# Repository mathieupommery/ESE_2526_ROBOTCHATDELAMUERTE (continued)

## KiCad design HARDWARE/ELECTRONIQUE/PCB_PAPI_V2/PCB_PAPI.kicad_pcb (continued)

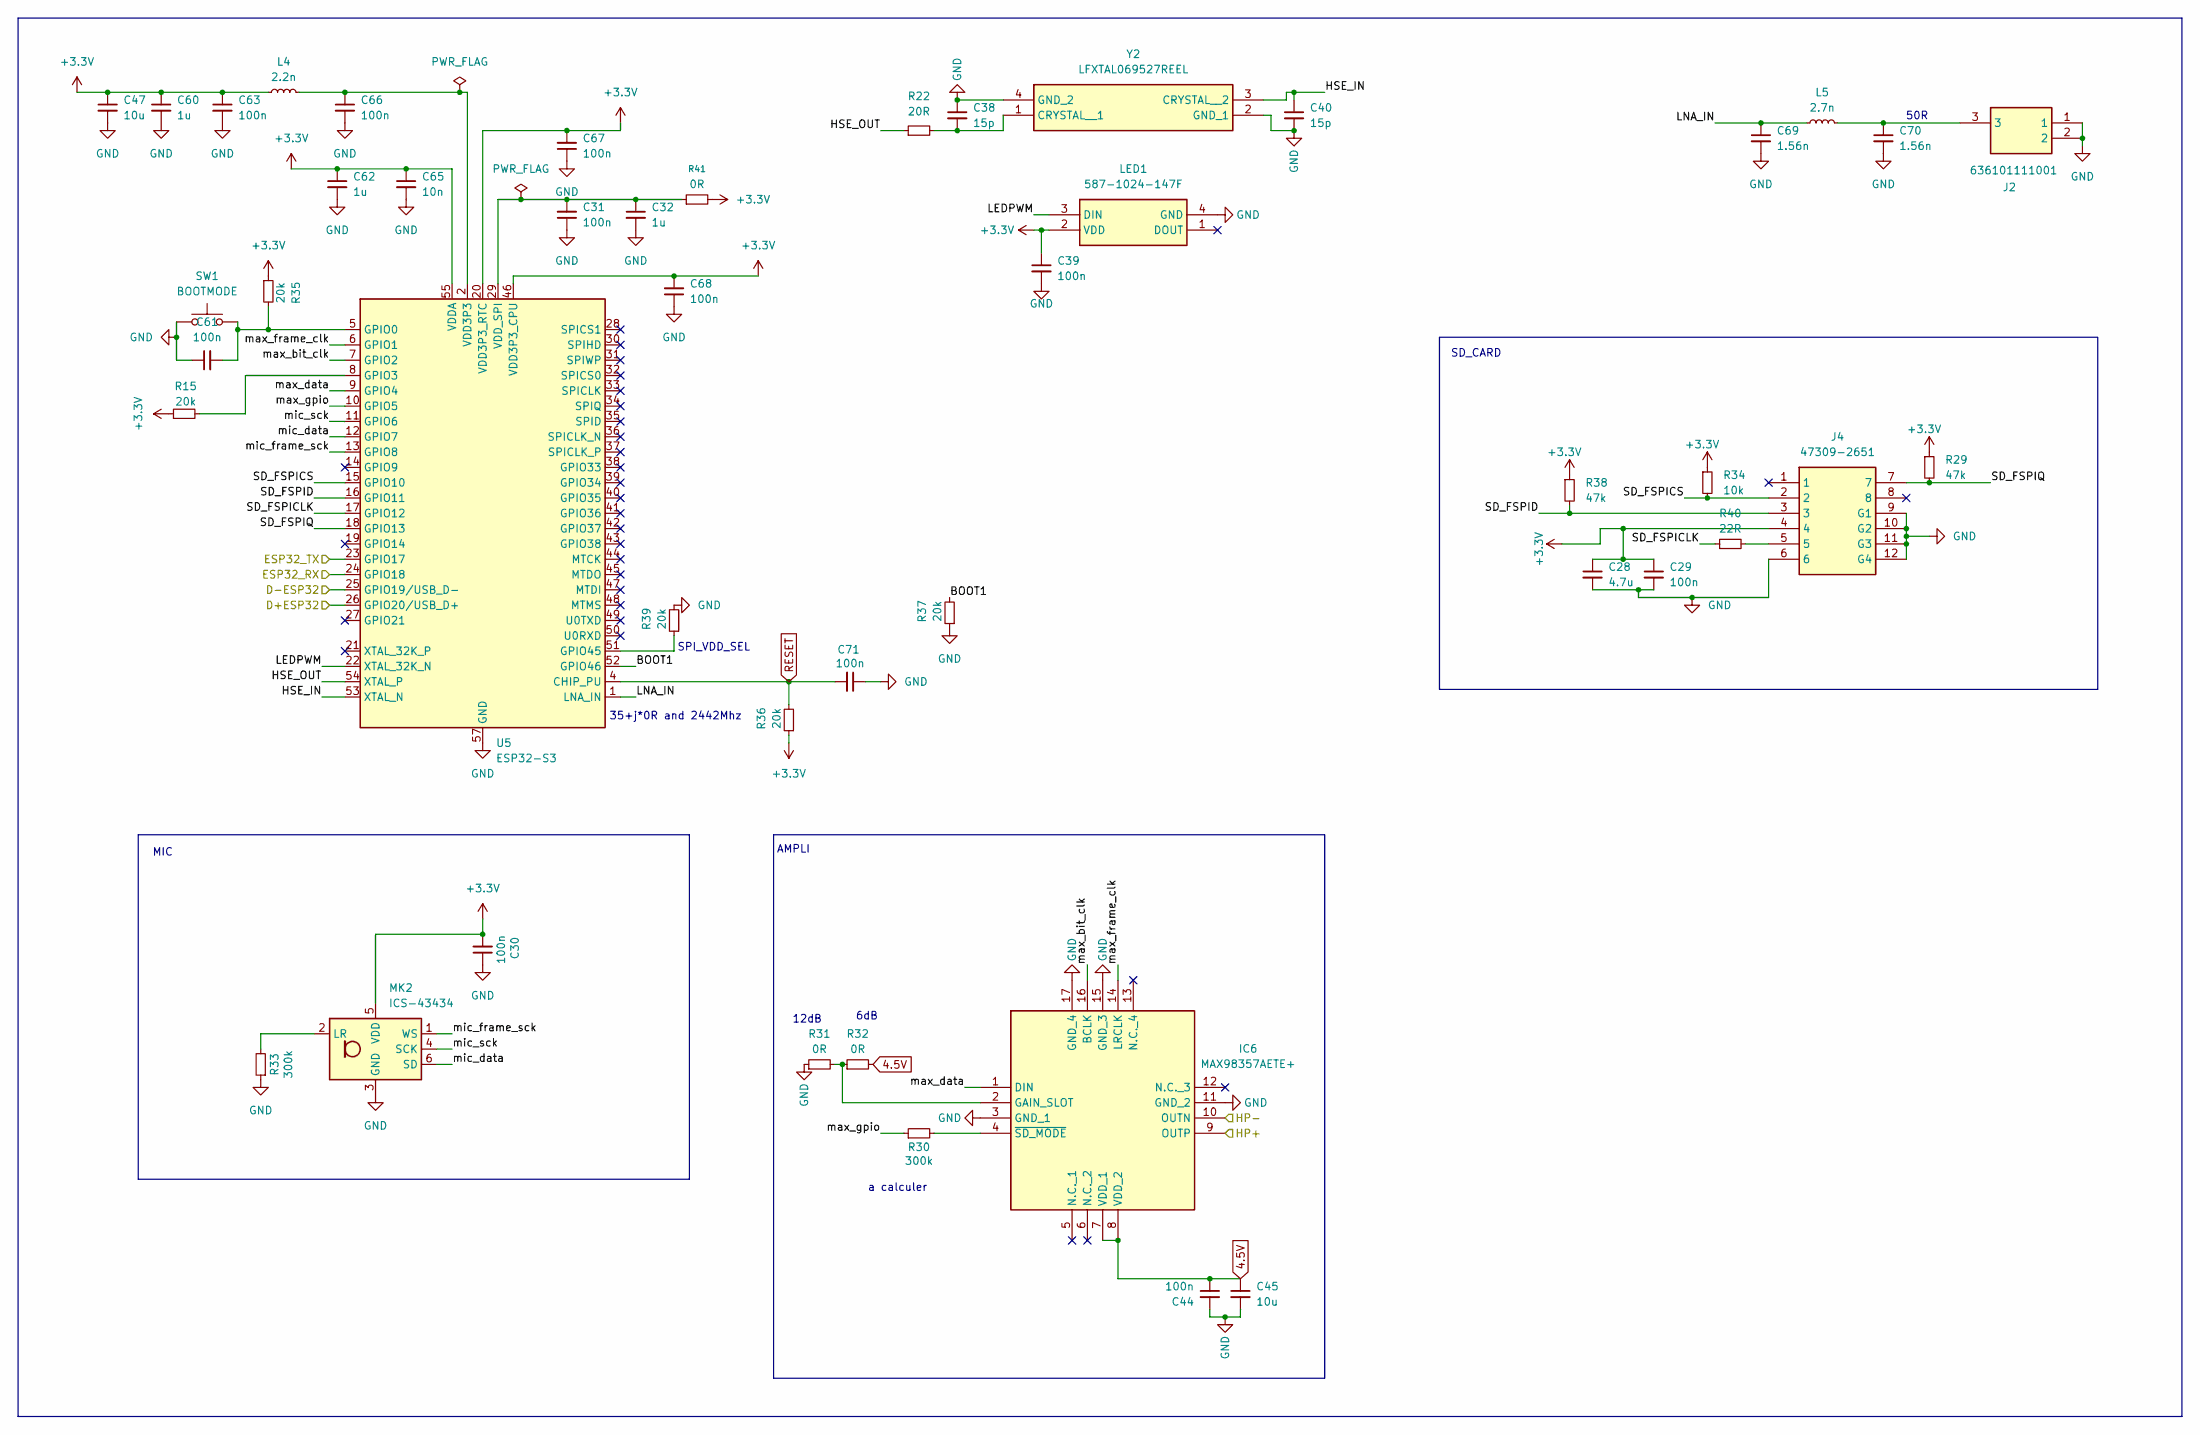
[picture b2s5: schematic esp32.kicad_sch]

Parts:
C28: 4.7u; C_0402_1005Metric_Pad0.74x0.62mm_HandSolder
C29, C39, C44: 100n; C_0201_0603Metric
C30, C31, C61, C63, C66, C67, C68, C71: 100n; C_0201_0603Metric_Pad0.64x0.40mm_HandSolder
C32, C60, C62: 1u; C_0402_1005Metric_Pad0.74x0.62mm_HandSolder
C38, C40: 15p; C_0201_custom
C45: 10u; C_0402_1005Metric; Manufacturer_Part_Number 885012105008; Mouser Part Number 710-885012105008
C47: 10u; C_0402_1005Metric_Pad0.74x0.62mm_HandSolder
C65: 10n; C_0201_0603Metric_Pad0.64x0.40mm_HandSolder
C69, C70: 1.56n; C_0402_1005Metric_Pad0.74x0.62mm_HandSolder
IC6: MAX98357AETE+; QFN50P300X300X80-17N; Manufacturer_Part_Number MAX98357AETE+; Mouser Part Number 700-MAX98357AETE+
J2: 636101111001; Mouser Part Number 710-636101111001
J4: 47309-2651; 473092651; Manufacturer_Part_Number 47309-2651
L4: 2.2n; L_0603_1608Metric
L5: 2.7n; L_0603_1608Metric
LED1: 587-1024-147F; 5871024147F; Manufacturer_Part_Number 587-1024-147F
MK2: ICS-43434; InvenSense_ICS-43434-6_3.5x2.65mm
R15, R35, R36, R37, R39: 20k; R_0201_0603Metric_Pad0.64x0.40mm_HandSolder
R22: 20R; R_0201_0603Metric
R29, R38: 47k; R_0201_0603Metric
R30, R33: 300k; R_0201_0603Metric; Manufacturer_Part_Number ERJ-1GNF1000C; Mouser Part Number 667-ERJ-1GNF1000C
R31: 0R; R_0201_custom; Manufacturer_Part_Number ERJ-1GNF1000C; Mouser Part Number 667-ERJ-1GNF1000C
R32: 0R; R_0201_0603Metric; Manufacturer_Part_Number ERJ-1GNF1000C; Mouser Part Number 667-ERJ-1GNF1000C
R34: 10k; R_0201_0603Metric
R40: 22R; R_0201_0603Metric
R41: 0R; R_0402_1005Metric_Pad0.72x0.64mm_HandSolder
SW1: BOOTMODE; KXT341LHS
U5: ESP32-S3; QFN-56-1EP_7x7mm_P0.4mm_EP4x4mm
Y2: LFXTAL069527REEL; Manufacturer_Part_Number LFXTAL069527REEL

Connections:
4.5V: C44.1, C45.1, IC6.7 (VDD_1), IC6.8 (VDD_2), R32.2; also elsewhere on the board
+3.3V: C28.1, C29.1, C30.2, C39.1, C47.1, C60.1, C62.1, C63.1, C65.1, C67.2, C68.2, J4.4, L4.1, LED1.2 (VDD), MK2.5 (VDD), R15.1, R29.1, R34.1, R35.1, R36.1, R38.1, R41.2, U5.20 (VDD3P3_RTC), U5.46 (VDD3P3_CPU), U5.55 (VDDA), U5.56 (VDDA); also elsewhere on the board
/D+ESP32: U5.26 (GPIO20/USB_D+); also elsewhere on the board
/D-ESP32: U5.25 (GPIO19/USB_D-); also elsewhere on the board
/ESP32/BOOT1: R37.2, U5.52 (GPIO46)
/ESP32/HSE_IN: C40.1, U5.53 (XTAL_N), Y2.3 (CRYSTAL__2)
/ESP32/HSE_OUT: R22.1, U5.54 (XTAL_P)
/ESP32/LEDPWM: LED1.3 (DIN), U5.22 (XTAL_32K_N)
/ESP32/LNA_IN: C69.1, L5.1, U5.1 (LNA_IN)
/ESP32/SD_FSPICLK: R40.1, U5.17 (GPIO12)
/ESP32/SD_FSPICS: J4.2, R34.2, U5.15 (GPIO10)
/ESP32/SD_FSPID: J4.3, R38.2, U5.16 (GPIO11)
/ESP32/SD_FSPIQ: J4.7, R29.2, U5.18 (GPIO13)
/ESP32/max_bit_clk: IC6.16 (BCLK), U5.7 (GPIO2)
/ESP32/max_data: IC6.1 (DIN), U5.9 (GPIO4)
/ESP32/max_frame_clk: IC6.14 (LRCLK), U5.6 (GPIO1)
/ESP32/max_gpio: R30.1, U5.10 (GPIO5)
/ESP32/mic_data: MK2.6 (SD), U5.12 (GPIO7)
/ESP32/mic_frame_sck: MK2.1 (WS), U5.13 (GPIO8)
/ESP32/mic_sck: MK2.4 (SCK), U5.11 (GPIO6)
/ESP32_RX: U5.24 (GPIO18); also elsewhere on the board
/ESP32_TX: U5.23 (GPIO17); also elsewhere on the board
/HP+: IC6.9 (OUTP); also elsewhere on the board
/HP-: IC6.10 (OUTN); also elsewhere on the board
GND: C28.2, C29.2, C30.1, C31.1, C32.2, C38.1, C39.2, C40.2, C44.2, C45.2, C47.2, C60.2, C61.1, C62.2, C63.2, C65.2, C66.2, C67.1, C68.1, C69.2, C70.2, C71.1, IC6.3 (GND_1), IC6.11 (GND_2), IC6.15 (GND_3), IC6.17 (GND_4), J2.1, J2.2, J4.6, J4.9 (G1), J4.10 (G2), J4.11 (G3), J4.12 (G4), LED1.4 (GND), MK2.3 (GND), R31.1, R33.1, R37.1, R39.2, SW1.1, U5.57 (GND), Y2.2 (GND_1), Y2.4 (GND_2); also elsewhere on the board
unnamed: C66.1, L4.2, U5.2 (VDD3P3), U5.3 (VDD3P3)
unnamed: C70.1, J2.3, L5.2
unnamed: IC6.2 (GAIN_SLOT), R31.2, R32.1
unnamed: IC6.4 (~SD_MODE), R30.2
unnamed: J4.5, R40.2
unnamed: MK2.2 (LR), R33.2
unnamed: C61.2, R35.2, SW1.2, U5.5 (GPIO0)
unnamed: R15.2, U5.8 (GPIO3)
unnamed: R39.1, U5.51 (GPIO45)
unnamed: C31.2, C32.1, R41.1, U5.29 (VDD_SPI)
unnamed: C38.2, R22.2, Y2.1 (CRYSTAL__1)
RESET: C71.2, R36.2, U5.4 (CHIP_PU)

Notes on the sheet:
50R
6dB
a calculer
12dB
MIC
35+j*0R and 2442Mhz
SD_CARD
AMPLI
SPI_VDD_SEL

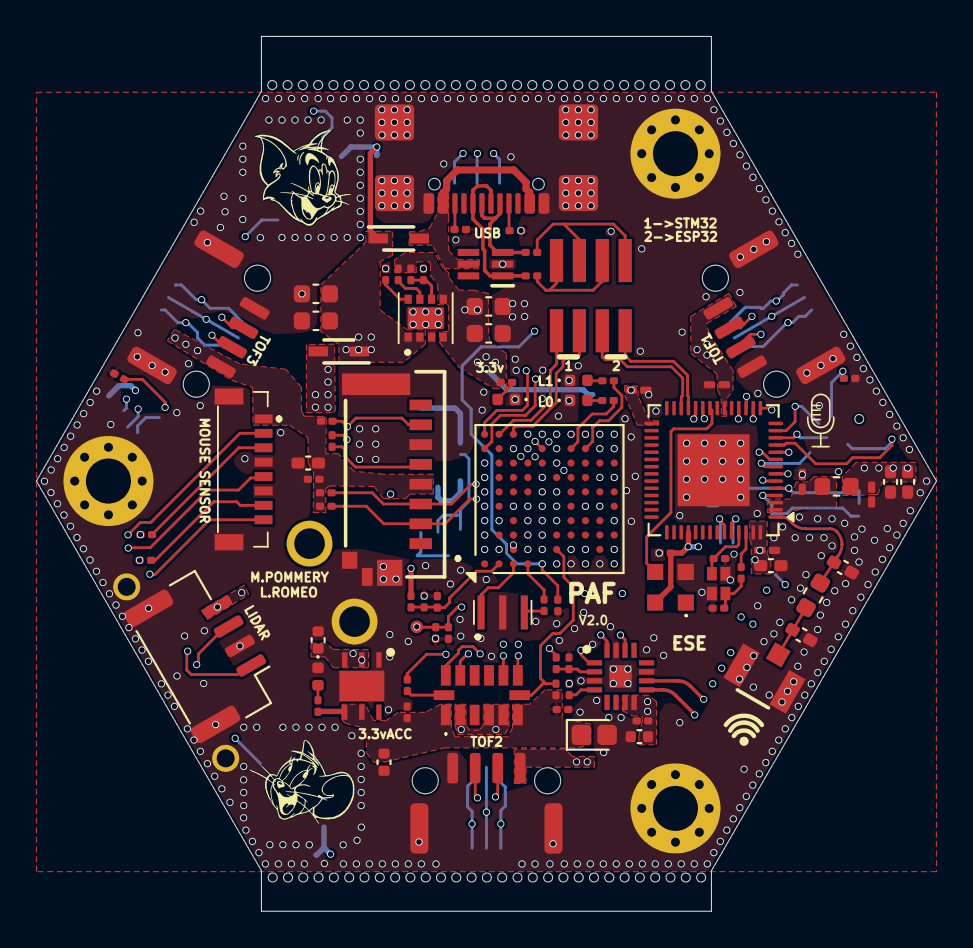
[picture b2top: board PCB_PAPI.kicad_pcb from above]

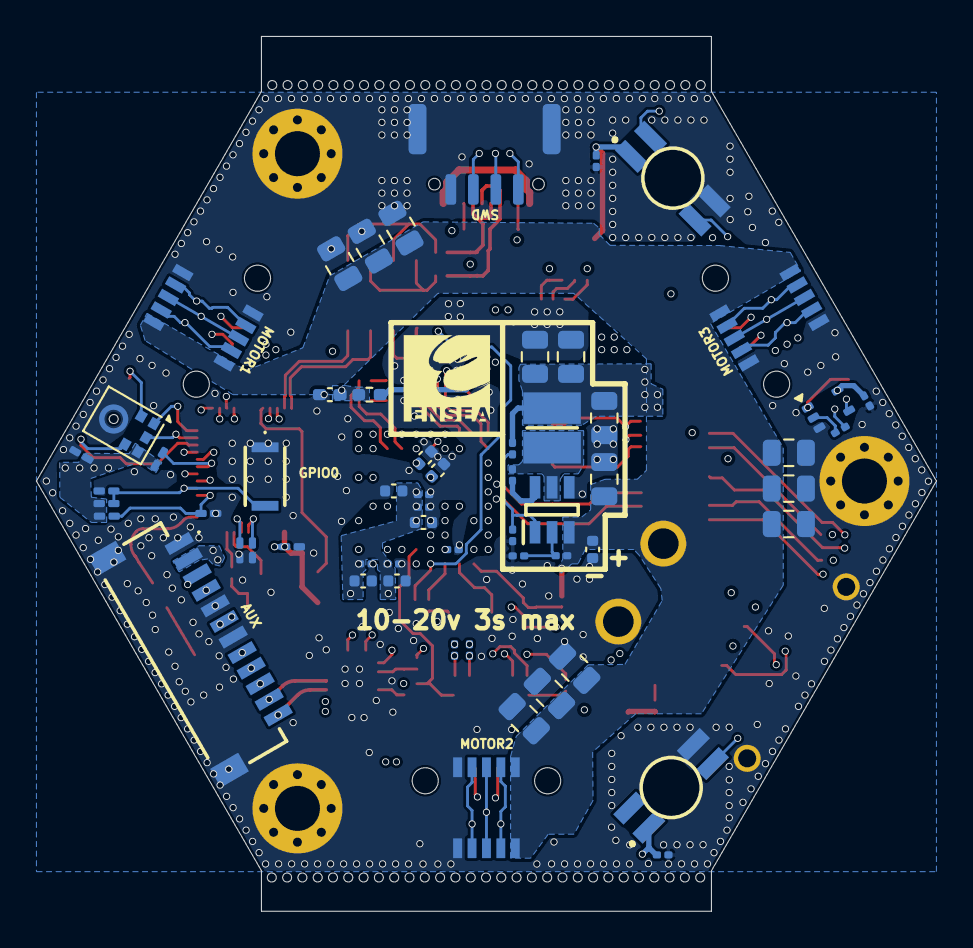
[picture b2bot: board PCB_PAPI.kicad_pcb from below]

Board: 8 copper layers, 50.0 x 48.6 mm, 150 parts (60 on the bottom side), 115 nets.

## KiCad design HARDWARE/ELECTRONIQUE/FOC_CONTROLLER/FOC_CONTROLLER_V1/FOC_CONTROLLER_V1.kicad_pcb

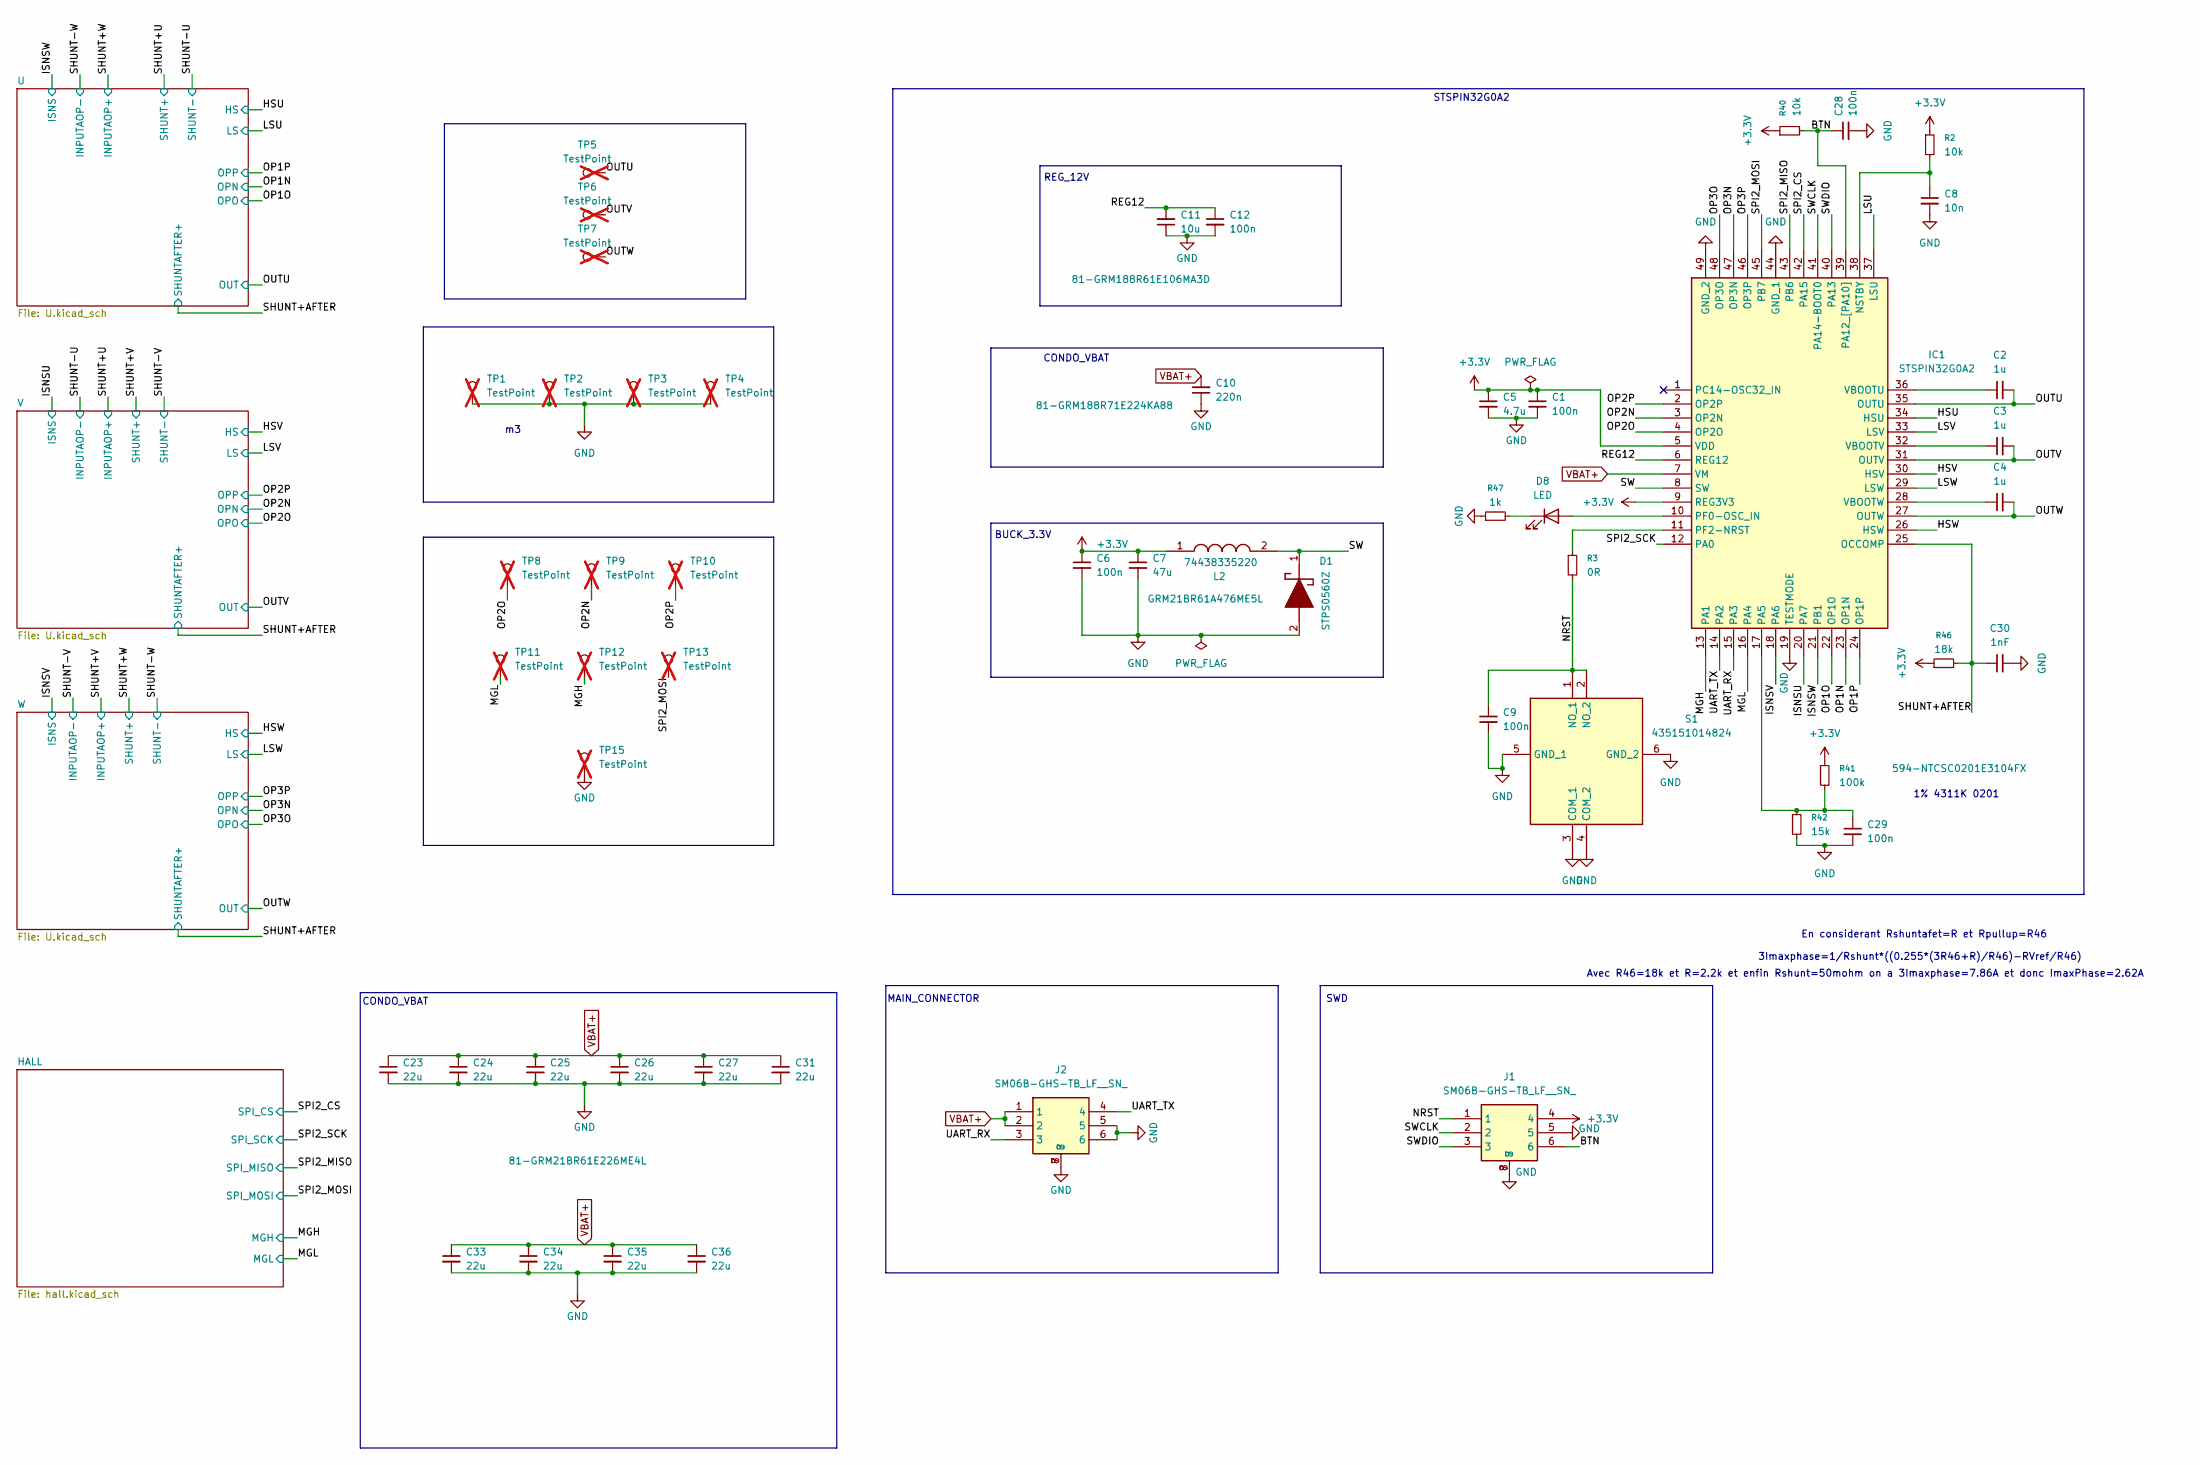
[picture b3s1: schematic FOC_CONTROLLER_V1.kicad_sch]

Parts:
C1, C6, C9, C12, C28, C29: 100n; C_0201_0603Metric_Pad0.64x0.40mm_HandSolder
C2, C3, C4: 1u; C_0603_1608Metric; Manufacturer_Part_Number GCM188M8EH105KE8D; Mouser Part Number 81-GCM188M8EH105KE8D
C5: 4.7u; C_0402_1005Metric
C7: 47u; C_0805_2012Metric; Manufacturer_Part_Number GRM21BR61A476ME5L; Mouser Part Number 81-GRM21BR61A476ME5L
C8: 10n; C_0201_0603Metric_Pad0.64x0.40mm_HandSolder
C10: 220n; C_0603_1608Metric; Manufacturer_Part_Number GRM188R71E224KA88; Mouser Part Number 81-GRM188R71E224KA88
C11: 10u; C_0603_1608Metric; Manufacturer_Part_Number GRM188R61E106MA3D; Mouser Part Number 81-GRM188R61E106MA3D
C23, C24, C25, C26, C27, C31, C33, C34, C35, C36: 22u; C_0805_2012Metric; Manufacturer_Part_Number GRM21BR61E226ME4L; Mouser Part Number 81-GRM21BR61E226ME4L
C30: 1nF; C_0201_0603Metric_Pad0.64x0.40mm_HandSolder
D1: STPS0560Z; Manufacturer_Part_Number STPS0560Z; Mouser Part Number 511-STPS0560Z
D8: LED; LED_0402_1005Metric
IC1: STSPIN32G0A2; QFN50P700X700X105-49N-D; Manufacturer_Part_Number STSPIN32G0A2; Mouser Part Number 511-STSPIN32G0A2
J1, J2: SM06B-GHS-TB_LF__SN_; SM06B-GHS-TB; Manufacturer_Part_Number SM06B-GHS-TB(LF)(SN); Mouser Part Number N/A
L2: 74438335220; Manufacturer_Part_Number 74438335220; Mouser Part Number 710-74438335220
R2, R40: 10k; R_0201_0603Metric_Pad0.64x0.40mm_HandSolder
R3: 0R; R_0201_0603Metric_Pad0.64x0.40mm_HandSolder
R41: 100k; R_0201_0603Metric_Pad0.64x0.40mm_HandSolder; Manufacturer_Part_Number NTCSC0201E3104FX; Mouser Part Number 594-NTCSC0201E3104FX
R42: 15k; R_0201_0603Metric_Pad0.64x0.40mm_HandSolder
R46: 18k; R_0201_0603Metric_Pad0.64x0.40mm_HandSolder
R47: 1k; R_0201_0603Metric_Pad0.64x0.40mm_HandSolder
S1: 435151014824; Mouser Part Number 710-435151014824
TP1, TP2, TP3, TP4: TestPoint; m3test; not fitted
TP5, TP6, TP7: TestPoint; hole_1.5mm; not fitted
TP8, TP9, TP10, TP11, TP12, TP13, TP15: TestPoint; pad_0.7mm; not fitted

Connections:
+3.3V: C1.1, C5.1, C6.1, C7.1, IC1.5 (VDD), IC1.9 (REG3V3), J1.4, L2.1, R2.1, R40.1, R41.1, R46.1; also elsewhere on the board
/BTN: C28.1, IC1.39 (PA12_[PA10]), J1.6, R40.2
/HSU: IC1.34 (HSU); also elsewhere on the board
/HSV: IC1.30 (HSV); also elsewhere on the board
/HSW: IC1.26 (HSW); also elsewhere on the board
/ISNSU: IC1.20 (PA7); also elsewhere on the board
/ISNSV: IC1.18 (PA6); also elsewhere on the board
/ISNSW: IC1.21 (PB1); also elsewhere on the board
/LSU: IC1.37 (LSU); also elsewhere on the board
/LSV: IC1.33 (LSV); also elsewhere on the board
/LSW: IC1.29 (LSW); also elsewhere on the board
/MGH: IC1.13 (PA1), TP12.1; also elsewhere on the board
/MGL: IC1.16 (PA4), TP11.1; also elsewhere on the board
/NRST: C9.1, J1.1, R3.2, S1.1 (NO_1), S1.2 (NO_2)
/OP1N: IC1.23 (OP1N); also elsewhere on the board
/OP1O: IC1.22 (OP1O); also elsewhere on the board
/OP1P: IC1.24 (OP1P); also elsewhere on the board
/OP2N: IC1.3 (OP2N), TP9.1; also elsewhere on the board
/OP2O: IC1.4 (OP2O), TP8.1; also elsewhere on the board
/OP2P: IC1.2 (OP2P), TP10.1; also elsewhere on the board
/OP3N: IC1.47 (OP3N); also elsewhere on the board
/OP3O: IC1.48 (OP3O); also elsewhere on the board
/OP3P: IC1.46 (OP3P); also elsewhere on the board
/OUTU: C2.2, IC1.35 (OUTU), TP5.1; also elsewhere on the board
/OUTV: C3.2, IC1.31 (OUTV), TP6.1; also elsewhere on the board
/OUTW: C4.2, IC1.27 (OUTW), TP7.1; also elsewhere on the board
/REG12: C11.2, C12.1, IC1.6 (REG12)
/SHUNT+AFTER: C30.1, IC1.25 (OCCOMP), R46.2; also elsewhere on the board
/SPI2_CS: IC1.42 (PA15); also elsewhere on the board
/SPI2_MISO: IC1.43 (PB6); also elsewhere on the board
/SPI2_MOSI: IC1.45 (PB7), TP13.1; also elsewhere on the board
/SPI2_SCK: IC1.12 (PA0); also elsewhere on the board
/SW: D1.1 (K), IC1.8 (SW), L2.2
/SWCLK: IC1.41 (PA14-BOOT0), J1.2
/SWDIO: IC1.40 (PA13), J1.3
/UART_RX: IC1.15 (PA3), J2.3
/UART_TX: IC1.14 (PA2), J2.4
GND: C1.2, C5.2, C6.2, C7.2, C8.2, C9.2, C10.1, C11.1, C12.2, C23.2, C24.2, C25.2, C26.2, C27.2, C28.2, C29.2, C30.2, C31.2, C33.2, C34.2, C35.2, C36.2, D1.2 (A), IC1.19 (TESTMODE), IC1.44 (GND_1), IC1.49 (GND_2), J1.5, J1.7, J1.8, J2.5, J2.6, J2.7, J2.8, R42.2, R47.1, S1.3 (COM_1), S1.4 (COM_2), S1.5 (GND_1), S1.6 (GND_2), TP1.1, TP2.1, TP3.1, TP4.1, TP15.1; also elsewhere on the board
unnamed: D8.2 (A), IC1.10 (PF0-OSC_IN)
unnamed: D8.1 (K), R47.2
unnamed: C8.1, IC1.38 (NSTBY), R2.2
unnamed: C29.1, IC1.17 (PA5), R41.2, R42.1
unnamed: IC1.11 (PF2-NRST), R3.1
unnamed: C2.1, IC1.36 (VBOOTU)
unnamed: C3.1, IC1.32 (VBOOTV)
unnamed: C4.1, IC1.28 (VBOOTW)
VBAT+: C10.2, C23.1, C24.1, C25.1, C26.1, C27.1, C31.1, C33.1, C34.1, C35.1, C36.1, IC1.7 (VM), J2.1, J2.2; also elsewhere on the board

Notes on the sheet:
BUCK_3.3V
MAIN_CONNECTOR
CONDO_VBAT
SWD
STSPIN32G0A2
REG_12V
En considerant Rshuntafet=R et Rpullup=R46
3Imaxphase=1/Rshunt*((0.255*(3R46+R)/R46)-RVref/R46)
Avec R46=18k et R=2.2k et enfin Rshunt=50mohm on a 3Imaxphase=7.86A et donc ImaxPhase=2.62A
1% 4311K 0201

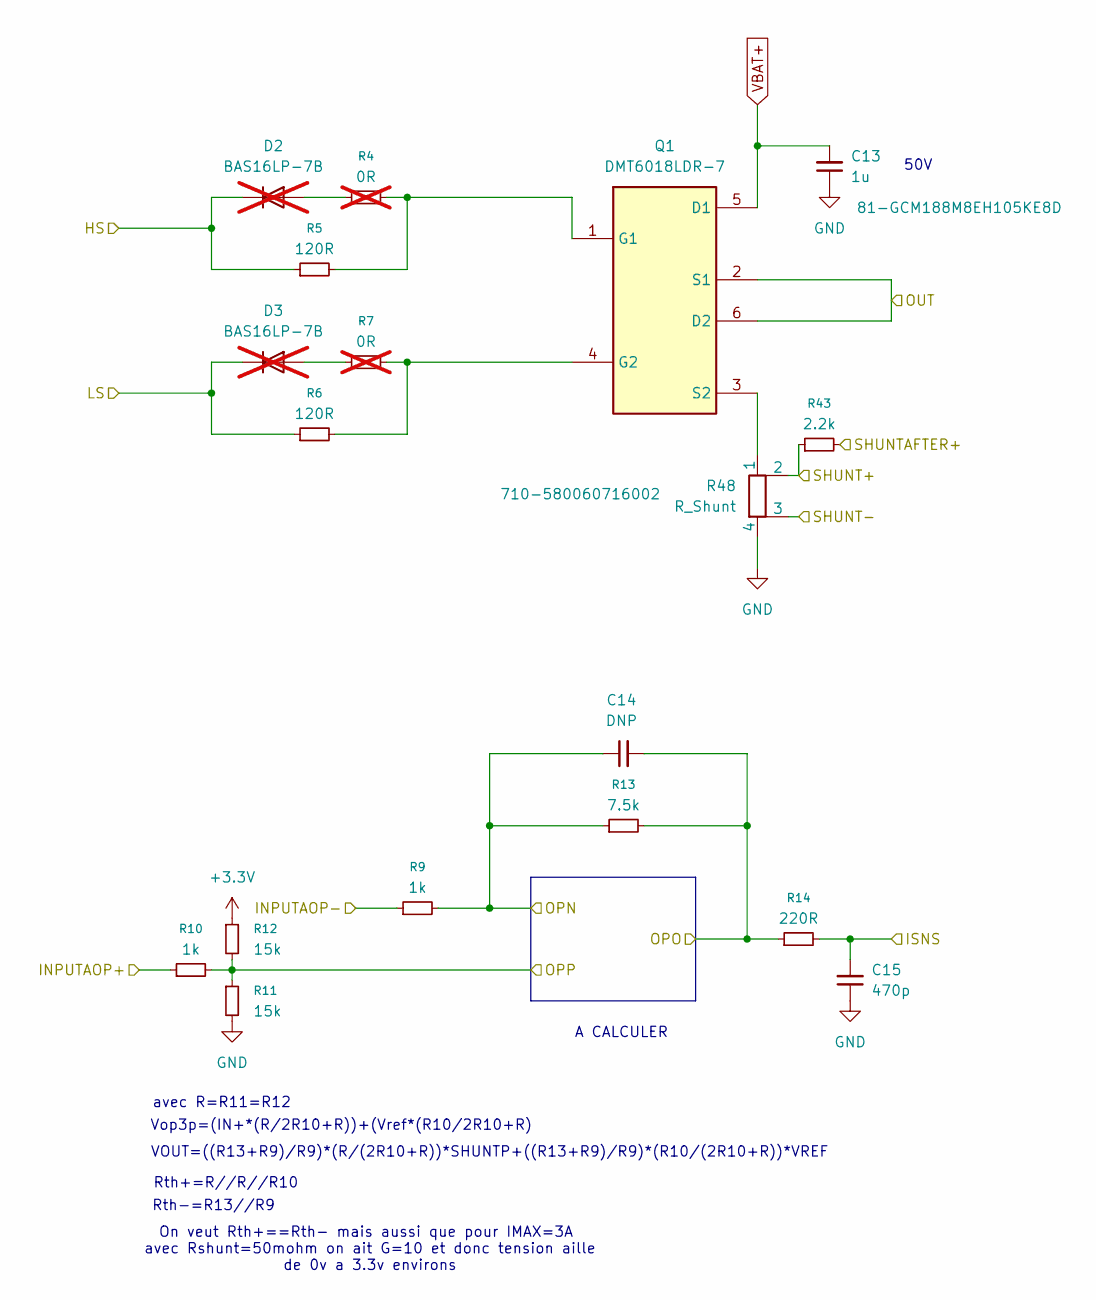
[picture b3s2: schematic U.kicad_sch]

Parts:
C13: 1u; C_0603_1608Metric; Manufacturer_Part_Number GCM188M8EH105KE8D; Mouser Part Number 81-GCM188M8EH105KE8D
C14: DNP; C_0201_0603Metric_Pad0.64x0.40mm_HandSolder
C15: 470p; C_0201_0603Metric_Pad0.64x0.40mm_HandSolder
D2, D3: BAS16LP-7B; D_01005_0402Metric_Pad0.57x0.30mm_HandSolder; not fitted
Q1: DMT6018LDR-7; DMT6018LDR7; Manufacturer_Part_Number DMT6018LDR-7; Mouser Part Number 621-DMT6018LDR-7
R4, R7: 0R; R_0201_0603Metric_Pad0.64x0.40mm_HandSolder; not fitted
R5, R6: 120R; R_0201_0603Metric_Pad0.64x0.40mm_HandSolder
R9, R10: 1k; R_0201_0603Metric_Pad0.64x0.40mm_HandSolder
R11, R12: 15k; R_0201_0603Metric_Pad0.64x0.40mm_HandSolder
R13: 7.5k; R_0201_0603Metric_Pad0.64x0.40mm_HandSolder
R14: 220R; R_0201_0603Metric_Pad0.64x0.40mm_HandSolder
R43: 2.2k; R_0201_0603Metric_Pad0.64x0.40mm_HandSolder
R48: R_Shunt; 4wire_0603; Manufacturer_Part_Number 580060716002; Mouser Part Number 710-580060716002

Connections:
+3.3V: R12.1; also elsewhere on the board
/HSU: D2.1 (K), R5.1; also elsewhere on the board
/ISNSW: C15.2, R14.2; also elsewhere on the board
/LSU: D3.1 (K), R6.1; also elsewhere on the board
/OP1N: C14.1, R9.2, R13.1; also elsewhere on the board
/OP1O: C14.2, R13.2, R14.1; also elsewhere on the board
/OP1P: R10.2, R11.1, R12.2; also elsewhere on the board
/OUTU: Q1.2 (S1), Q1.6 (D2); also elsewhere on the board
/SHUNT+AFTER: R43.2; also elsewhere on the board
/SHUNT+U: R43.1, R48.2; also elsewhere on the board
/SHUNT+W: R10.1; also elsewhere on the board
/SHUNT-U: R48.3; also elsewhere on the board
/SHUNT-W: R9.1; also elsewhere on the board
GND: C13.1, C15.1, R11.2, R48.4; also elsewhere on the board
unnamed: D2.2 (A), R4.1
unnamed: D3.2 (A), R7.1
unnamed: Q1.1 (G1), R4.2, R5.2
unnamed: Q1.4 (G2), R6.2, R7.2
unnamed: Q1.3 (S2), R48.1
VBAT+: C13.2, Q1.5 (D1); also elsewhere on the board

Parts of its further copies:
C16, C19: DNP; C_0201_0603Metric_Pad0.64x0.40mm_HandSolder
C17, C20: 1u; C_0603_1608Metric; Manufacturer_Part_Number GCM188M8EH105KE8D; Mouser Part Number 81-GCM188M8EH105KE8D
C18, C21: 470p; C_0201_0603Metric_Pad0.64x0.40mm_HandSolder
D4, D5, D6, D7: BAS16LP-7B; D_01005_0402Metric_Pad0.57x0.30mm_HandSolder; not fitted
Q2, Q3: DMT6018LDR-7; DMT6018LDR7; Manufacturer_Part_Number DMT6018LDR-7; Mouser Part Number 621-DMT6018LDR-7
R15, R22, R26, R33: 1k; R_0201_0603Metric_Pad0.64x0.40mm_HandSolder
R16, R17, R27, R28: 15k; R_0201_0603Metric_Pad0.64x0.40mm_HandSolder
R18, R19, R29, R30: 120R; R_0201_0603Metric_Pad0.64x0.40mm_HandSolder
R20, R21, R31, R32: 0R; R_0201_0603Metric_Pad0.64x0.40mm_HandSolder; not fitted
R23, R34: 7.5k; R_0201_0603Metric_Pad0.64x0.40mm_HandSolder
R25, R36: 220R; R_0201_0603Metric_Pad0.64x0.40mm_HandSolder
R44, R45: 2.2k; R_0201_0603Metric_Pad0.64x0.40mm_HandSolder
R49, R50: R_Shunt; 4wire_0603; Manufacturer_Part_Number 580060716002; Mouser Part Number 710-580060716002

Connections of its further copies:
+3.3V: R16.1, R27.1; also elsewhere on the board
/HSV: D4.1 (K), R18.1; also elsewhere on the board
/HSW: D6.1 (K), R29.1; also elsewhere on the board
/ISNSU: C18.2, R25.2; also elsewhere on the board
/ISNSV: C21.2, R36.2; also elsewhere on the board
/LSV: D5.1 (K), R19.1; also elsewhere on the board
/LSW: D7.1 (K), R30.1; also elsewhere on the board
/OP2N: C16.1, R22.2, R23.1; also elsewhere on the board
/OP2O: C16.2, R23.2, R25.1; also elsewhere on the board
/OP2P: R15.2, R16.2, R17.1; also elsewhere on the board
/OP3N: C19.1, R33.2, R34.1; also elsewhere on the board
/OP3O: C19.2, R34.2, R36.1; also elsewhere on the board
/OP3P: R26.2, R27.2, R28.1; also elsewhere on the board
/OUTV: Q2.2 (S1), Q2.6 (D2); also elsewhere on the board
/OUTW: Q3.2 (S1), Q3.6 (D2); also elsewhere on the board
/SHUNT+AFTER: R44.2, R45.2; also elsewhere on the board
/SHUNT+U: R15.1; also elsewhere on the board
/SHUNT+V: R26.1, R44.1, R49.2
/SHUNT+W: R45.1, R50.2; also elsewhere on the board
/SHUNT-U: R22.1; also elsewhere on the board
/SHUNT-V: R33.1, R49.3
/SHUNT-W: R50.3; also elsewhere on the board
GND: C17.1, C18.1, C20.1, C21.1, R17.2, R28.2, R49.4, R50.4; also elsewhere on the board
unnamed: D4.2 (A), R20.1
unnamed: D5.2 (A), R21.1
unnamed: D6.2 (A), R31.1
unnamed: D7.2 (A), R32.1
unnamed: Q2.1 (G1), R18.2, R20.2
unnamed: Q2.4 (G2), R19.2, R21.2
unnamed: Q2.3 (S2), R49.1
unnamed: Q3.1 (G1), R29.2, R31.2
unnamed: Q3.4 (G2), R30.2, R32.2
unnamed: Q3.3 (S2), R50.1
VBAT+: C17.2, C20.2, Q2.5 (D1), Q3.5 (D1); also elsewhere on the board

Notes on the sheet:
VOUT=((R13+R9)/R9)*(R/(2R10+R))*SHUNTP+((R13+R9)/R9)*(R10/(2R10+R))*VREF
Rth+=R//R//R10
Vop3p=(IN+*(R/2R10+R))+(Vref*(R10/2R10+R)
avec R=R11=R12
50V
A CALCULER
Rth-=R13//R9
On veut Rth+==Rth- mais aussi que pour IMAX=3A avec Rshunt=50mohm on ait G=10 et donc tension aille de 0v a 3.3v environs

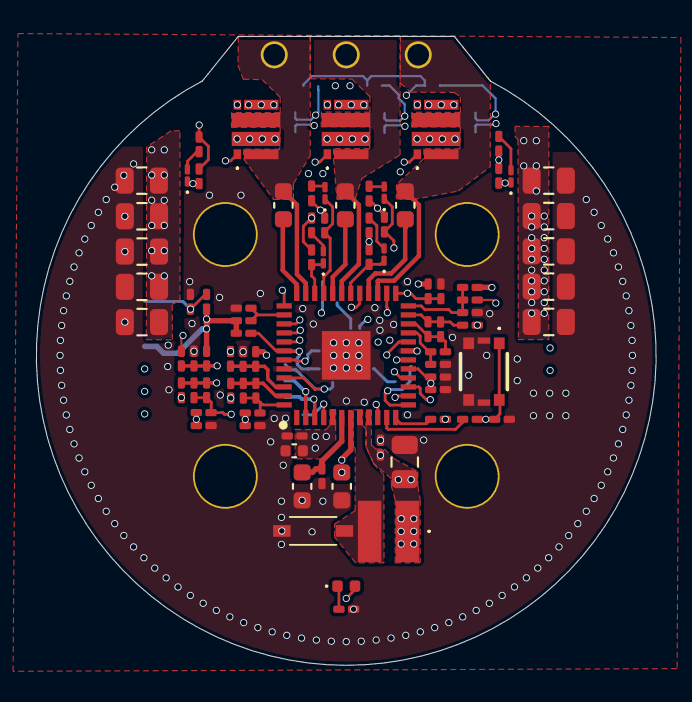
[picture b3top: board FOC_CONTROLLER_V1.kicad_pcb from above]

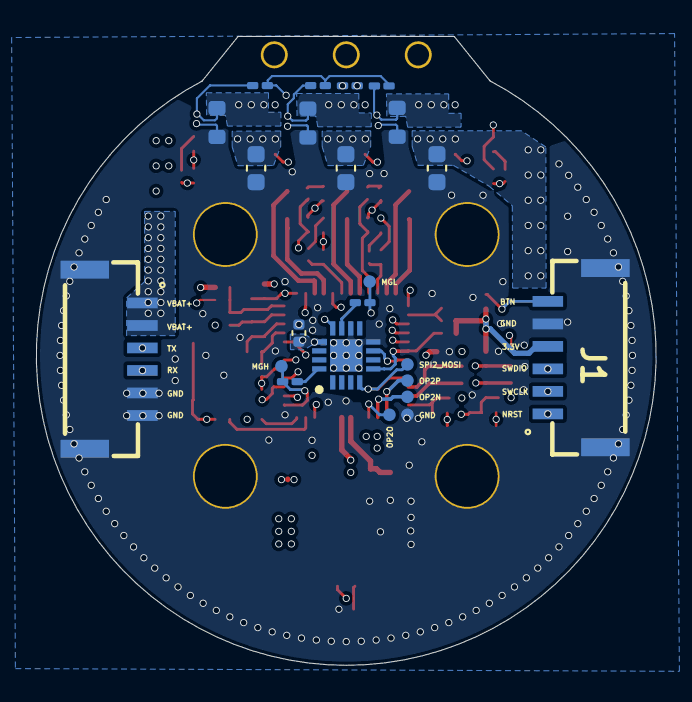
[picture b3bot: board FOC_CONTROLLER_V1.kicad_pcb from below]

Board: 8 copper layers, 34.4 x 34.9 mm, 113 parts (23 on the bottom side), 71 nets.

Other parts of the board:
C22: 1u; C_0402_1005Metric
IC2: MA330GQ-Z; QFN50P300X300X100-17N-D
R1: 10k; R_0201_0603Metric_Pad0.64x0.40mm_HandSolder
R37: 100R; R_0201_0603Metric_Pad0.64x0.40mm_HandSolder
R38, R39: 0R; R_0201_0603Metric_Pad0.64x0.40mm_HandSolder
TP1#2, TP1#3, TP1#4: TestPoint; m3test

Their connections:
+3.3V: C22.1, IC2.13 (VDD), R1.2; also elsewhere on the board
/MGH: R39.2; also elsewhere on the board
/MGL: R38.1; also elsewhere on the board
/SPI2_CS: IC2.5 (CS), R1.1; also elsewhere on the board
/SPI2_MISO: IC2.7 (MISO); also elsewhere on the board
/SPI2_MOSI: IC2.4 (MOSI); also elsewhere on the board
/SPI2_SCK: R37.1; also elsewhere on the board
GND: C22.2, IC2.8 (GND), IC2.10 (TEST), IC2.17 (EP), TP1#2.1, TP1#3.1, TP1#4.1; also elsewhere on the board
unnamed: IC2.16 (MGH), R39.1
unnamed: IC2.11 (MGL), R38.2
unnamed: IC2.12 (SCLK), R37.2
